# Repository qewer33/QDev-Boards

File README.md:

# QDev Boards

QDev Boards is a series of development boards that are inexpensive, simple and easy to order and assemble for beginner hobbyists.

This repository currently only has one entry but I plan to add more as I design and protoype new boards.

I am still fairly new and inexperienced when it comes to electronics and PCB design so if you have any suggestions or critics, please send them my way.

## Series

QDev Tiny (ATtiny25/45/85-PU): https://github.com/qewer33/QDev-Boards/tree/main/QDevTiny

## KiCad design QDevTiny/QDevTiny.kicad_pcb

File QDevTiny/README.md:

## QDev Tiny

| Property        | Value             |
| --------------- | ----------------- |
| Revision        | 1                 |
| Microcontroller | ATtiny25/45/85-PU |
| ISP Connector   | Yes               |
| USB Support     | Yes (software)    |
| GPIO Count      | 6 (1 passive)     |

### Description

QDevTiny is a small board that is built around the Atmel ATTiny25/45/85 microcontroller. It has an 8 pin header, 6 of them being GPIO pins. It also includes an ISP programming header for easy use with Atmel programmers. The board has a USB Type-A male edge connector for power and USB programming. USB programming requires the Micronucleus bootloader (which provides software USB support for certain Atmel microcontrollers) to be flashed.

### Supported Microcontroller Chips

| Microcontroller   | Flash | SRAM | EEPROM |
| ----------------- | ----- | ---- | ------ |
| ATtiny25          | 2KB   | 128B | 128B   |
| ATtiny45          | 4KB   | 256B | 256B   |
| ATtiny85          | 8KB   | 512B | 512B   |

### Setup Instructions

These instructions are for Linux. For other operating systems, the provided commands may be different.

1. To burn the Micronucleus bootloader, you need an Arduino UNO/Mega/Nano or an AVR ISP programmer. Open the `Examples > Arduino ISP` sketch in Arduino IDE, uncomment the line with `#define USE_OLD_STYLE_WIRING` and upload it to your Arduino board.

2. Open the Arduino IDE preferences and add the ATtiny Core library JSON link (http://drazzy.com/package_drazzy.com_index.json) to "Board Manager URLs" section. Wait for the Arduino IDE to process it and then install the ATtiny Core package from the Boards Manager.

3. Wire the QDev Tiny pins to the Arduino for programming.
    - 5V -> VCC
    - GND -> GND
    - 10 -> R/IO5
    - 11 -> IO0
    - 12 -> IO1
    - 13 -> IO2

4. Download the Micronucleus ATtiny85 binary from: https://raw.githubusercontent.com/micronucleus/micronucleus/master/firmware/releases/t85_default.hex

5. Open the terminal  in the folder you downloaded the Micronucleus binary in and run the following command. Replace `/dev/ttyUSB0` with the correct port if necessary.

```sh
sudo avrdude -c arduino -b 19200 -P /dev/ttyUSB0 -p t85 -U flash:w:t85_default.hex -U lfuse:w:0xF1:m -U hfuse:w:0xDD:m -U efuse:w:0xFE:m
```

Micronucleus should now be flashed. Disconnect the programming pins and plug your board into your computer. Check the output of the `lsusb` command. Your board should show up as `MCS Digistump DigiSpark`.

To upload a program to your board via USB, export your program via `Sketch > Export Compiled Binary`. Open the terminal in the build folder of your sketch and run the following command (change "your_program_name.hex" with the hex file of your program):

```sh
avrdude -c micronucleus -p t85 -x wait -V -U flash:w:your_program_name.hex
```

You can also download the Micronucleus CLI tool from https://github.com/micronucleus/micronucleus/releases/tag/v2.6 and use it to upload your programs:

```sh
micronucleus your_program_name.hex
```

You may need to press the reset button before uploading your program.

### Images

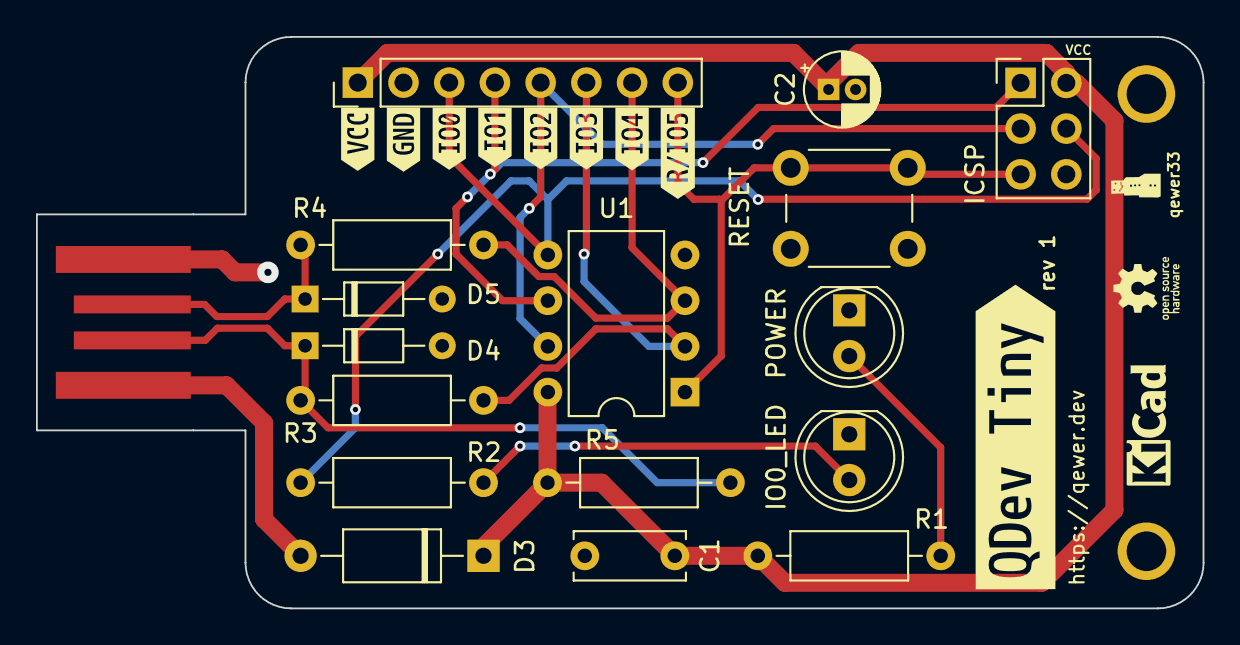
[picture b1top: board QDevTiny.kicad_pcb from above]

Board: 2 copper layers, 64.8 x 31.8 mm, 26 parts (0 on the bottom side), 13 nets.

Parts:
C1: 0.1uF; C_Disc_D6.0mm_W2.5mm_P5.00mm
C2: 4.7uF; CP_Radial_D4.0mm_P1.50mm
D1: PWR_LED; LED_D5.0mm
D2: PB0_LED; LED_D5.0mm
D3: D; D_A-405_P10.16mm_Horizontal
D4, D5: 3.6V; D_DO-34_SOD68_P7.62mm_Horizontal
J1: USB_A; USB-A-PCB
J2: Header; PinHeader_1x08_P2.54mm_Vertical
J3: ICSP; PinHeader_2x03_P2.54mm_Vertical
R1, R2, R5: 1K; R_Axial_DIN0207_L6.3mm_D2.5mm_P10.16mm_Horizontal
R3, R4: 68R; R_Axial_DIN0207_L6.3mm_D2.5mm_P10.16mm_Horizontal
SW1: RESET_BTN; SW_PUSH_6mm
U1: ATtiny45-20P; DIP-8_W7.62mm
kibuzzard-63E3F582: G***; kibuzzard-63E3F582
kibuzzard-63E24FBF: G***; kibuzzard-63E24FBF
kibuzzard-63E51F9F: G***; kibuzzard-63E51F9F
kibuzzard-63E51F81: G***; kibuzzard-63E51F81
kibuzzard-63E51F95: G***; kibuzzard-63E51F95
kibuzzard-63E51FA9: G***; kibuzzard-63E51FA9
kibuzzard-63E51FAF: G***; kibuzzard-63E51FAF
kibuzzard-63E51FB7: G***; kibuzzard-63E51FB7
kibuzzard-63E270EC: G***; kibuzzard-63E270EC

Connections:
+5V: C1.1, C2.1, D3.1 (K), J2.1, J3.2 (VCC), R1.1, R5.1, U1.8 (VCC)
/D+: D5.1 (K), J1.3 (D+), R4.1
/D-: D4.1 (K), J1.2 (D-), R3.1, R5.2
GND: C1.2, C2.2, D1.1 (K), D2.1 (K), D4.2 (A), D5.2 (A), J1.4 (GND), J2.2, J3.6 (GND), SW1.2, U1.4 (GND)
unnamed: D1.2 (A), R1.2
unnamed: D2.2 (A), R2.2
unnamed: D3.2 (A), J1.1 (VBUS)
PB0: J2.3, J3.4 (MOSI), R2.1, U1.5 (AREF/PB0)
PB1: J2.4, J3.1 (MISO), U1.6 (PB1)
PB2: J2.5, J3.3 (SCK), U1.7 (PB2)
PB3: J2.6, R3.2, U1.2 (XTAL1/PB3)
PB4: J2.7, R4.2, U1.3 (XTAL2/PB4)
PB5/R: J2.8, J3.5 (~RST), SW1.1, U1.1 (~RESET/PB5)

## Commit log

2023-02-26 Start new board and update QDev Tiny README
